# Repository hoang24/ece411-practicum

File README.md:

# Team 4: ECE 411 Practicum Repo

This is Team 4's Github repo for ECE411 Practicum. Codes and documents such as Product Design Specification (PDS) and Project Ideas can be found here.

### Team members:
- Jonathan Christian
- Hoang Nguyen
- Ngan Ho
- Karla Barraza

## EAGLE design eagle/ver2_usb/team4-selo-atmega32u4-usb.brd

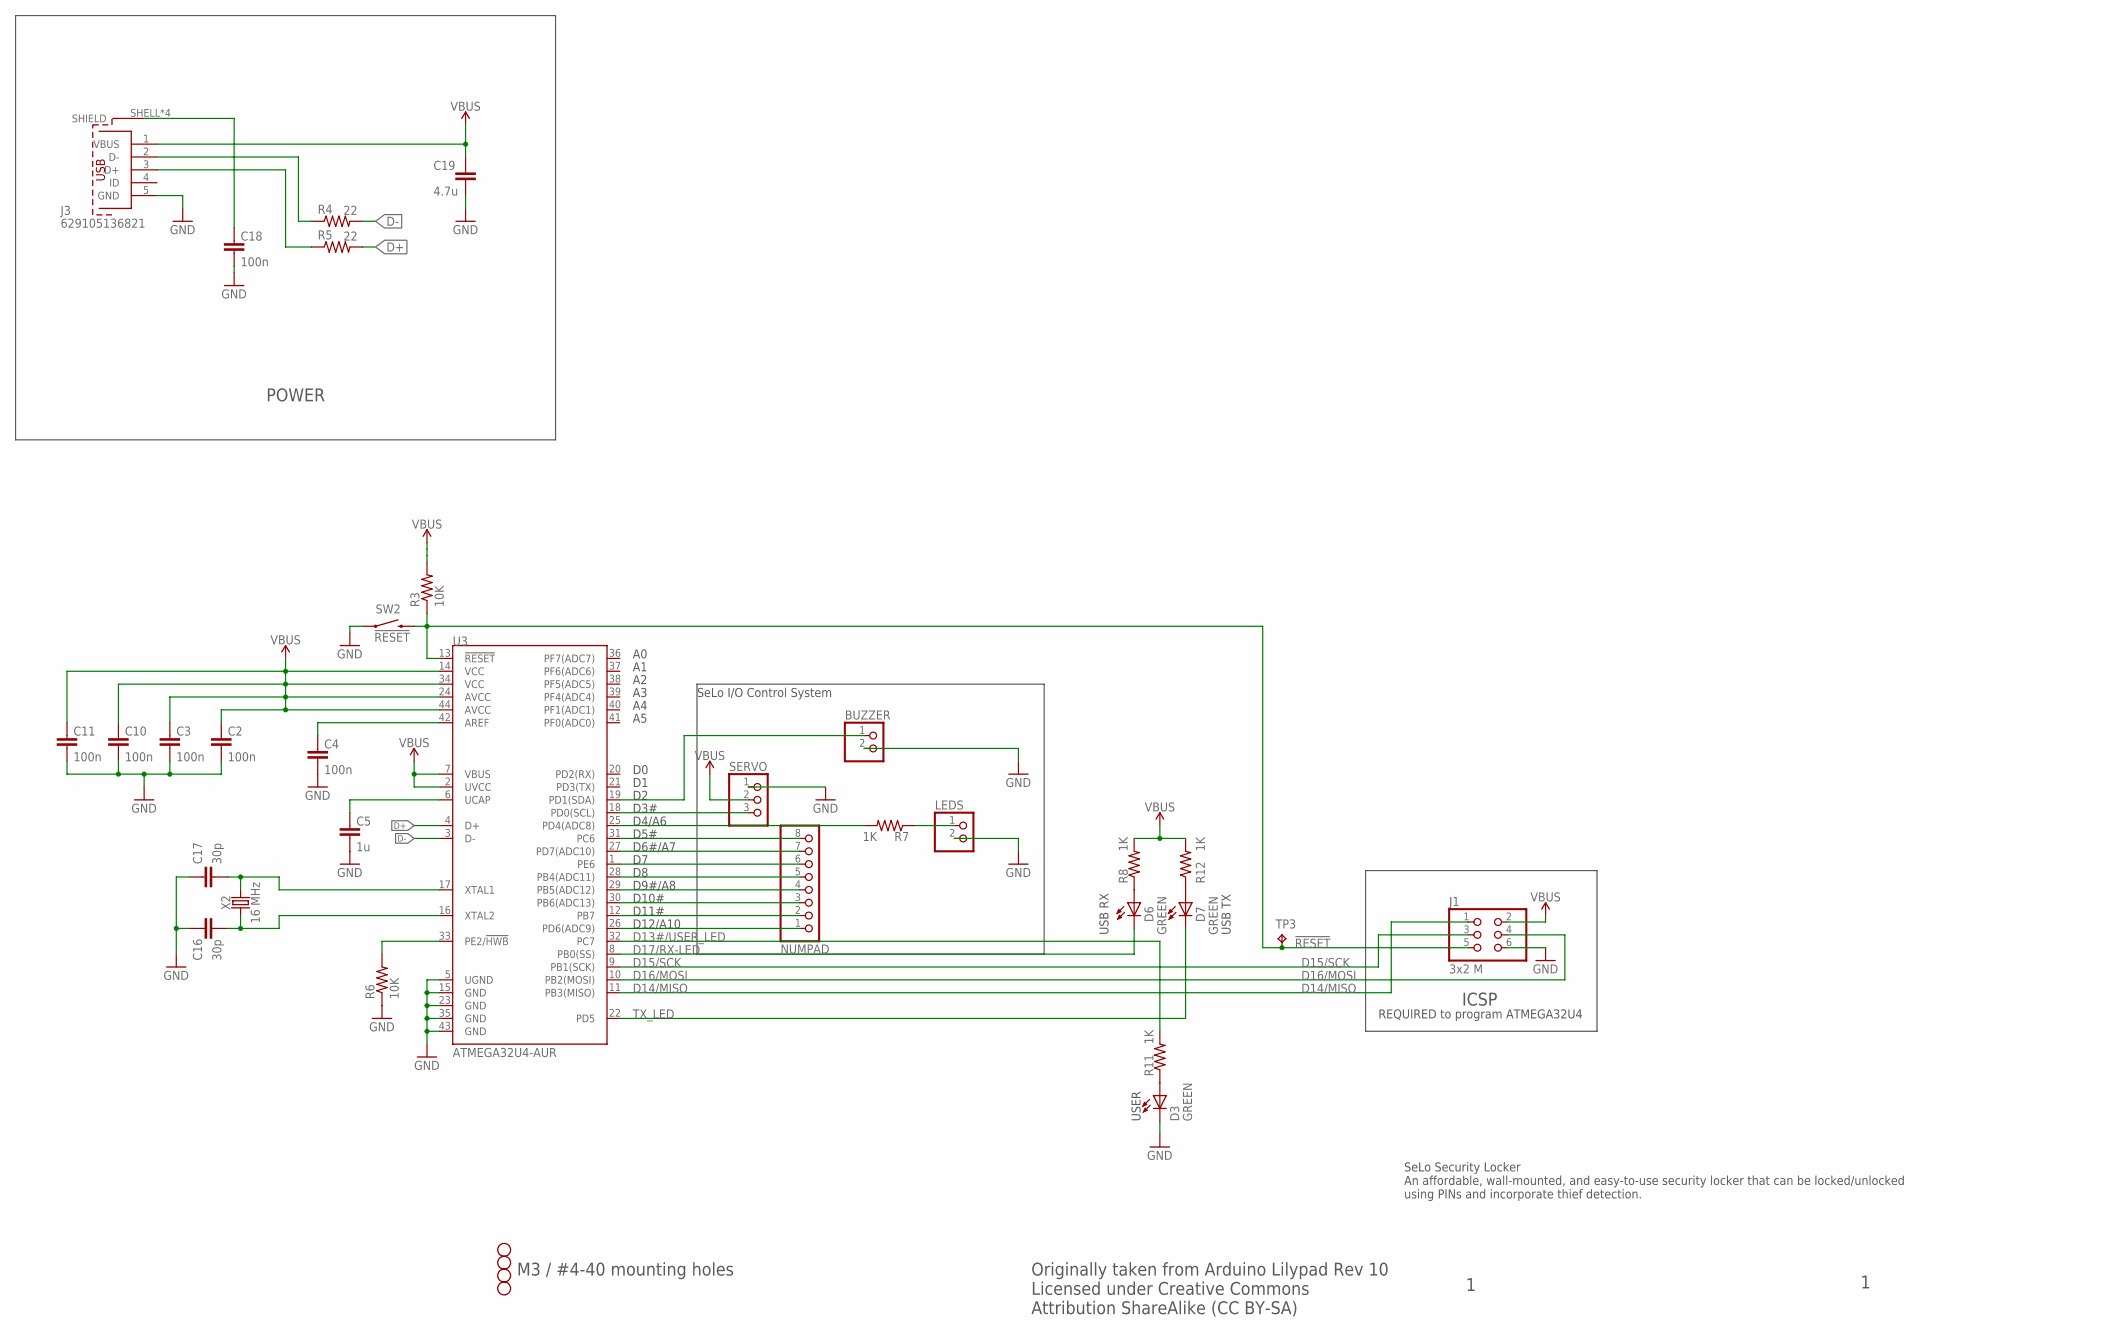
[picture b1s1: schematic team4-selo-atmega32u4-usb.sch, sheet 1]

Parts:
BUZZER: PINHD-1X2; 1X02
C2, C3, C4, C10, C11, C18: 100n; C0805K; MPN CL21B104KBCNNNC
C5: 1u; C0805K; MPN CL21B105KOFNNNG
C16: 30p; C0805K; MPN CL21C300JBANNNC
C17: 30p; C0805K; MPN CL21C180JBANNNC
C19: 4.7u; C0805K; MPN CL21A475KOFNNNE
D3, D6, D7: GREEN; CHIP-LED0805; MPN 150080GS75000
H1, H2, H3, H4: STAND-OFF
J1: 3x2 M; 2X03; MPN M20-9980345
J3: 629105136821; MPN 629105136821
LEDS: PINHD-1X2; 1X02
NUMPAD: PINHD-1X8; 1X08
R3, R6: 10K; R0805; MPN RC0805FR-0710KL
R4, R5: 22; R0805; MPN RC0805FR-0722RL
R7, R8, R11, R12: 1K; R0805; MPN RC0805FR-071KL
SERVO: PINHD-1X3; 1X03
SW2: !RESET; TACTILE_SWITCH_SMD; MPN RS-187R05A2-DS MT RT
TP3: TPPAD1-13; P1-13
U3: ATMEGA32U4-AUR; TQFP44; MPN ATMEGA32U4-AUR
X2: 16 MHz; HC49UP; MPN ECS-160-18-5PX-TR

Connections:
!RESET: J1.5, R3.1, SW2.3 (2), TP3.TP, U3.13 (!RESET)
AREF: C4.1, U3.42 (AREF)
D13#/USER_LED: R11.2, U3.32 (PC7)
D14/MISO: J1.1, U3.11 (PB3(MISO))
D15/SCK: J1.3, U3.9 (PB1(SCK))
D16/MOSI: J1.4, U3.10 (PB2(MOSI))
D17/RX-LED: D6.C, U3.8 (PB0(SS))
D+: R5.2, U3.4 (D+)
D-: R4.2, U3.3 (D-)
GND: BUZZER.2, C2.2, C3.2, C4.2, C5.2, C10.2, C11.2, C16.2, C17.2, C18.2, C19.2, D3.C, J1.6, J3.5 (GND), LEDS.2, R6.1, SERVO.1, SW2.1, U3.5 (UGND), U3.15 (GND), U3.23 (GND), U3.35 (GND), U3.43 (GND)
unnamed: SERVO.3, U3.18 (PD0(SCL))
unnamed: NUMPAD.8, U3.31 (PC6)
unnamed: NUMPAD.7, U3.27 (PD7(ADC10))
unnamed: NUMPAD.6, U3.1 (PE6)
unnamed: NUMPAD.5, U3.28 (PB4(ADC11))
unnamed: NUMPAD.4, U3.29 (PB5(ADC12))
unnamed: NUMPAD.3, U3.30 (PB6(ADC13))
unnamed: NUMPAD.2, U3.12 (PB7)
unnamed: NUMPAD.1, U3.26 (PD6(ADC9))
unnamed: D3.A, R11.1
unnamed: C18.1, J3.SHELL (SHIELD), J3.SHELL1 (SHIELD), J3.SHELL2 (SHIELD), J3.SHELL3 (SHIELD)
unnamed: D6.A, R8.1
unnamed: D7.A, R12.1
unnamed: R7.2, U3.25 (PD4(ADC8))
unnamed: LEDS.1, R7.1
unnamed: J3.2 (D-), R4.1
unnamed: J3.3 (D+), R5.1
unnamed: BUZZER.1, U3.19 (PD1(SDA))
PE2/!HWB: R6.2, U3.33 (PE2/!HWB)
TX_LED: D7.C, U3.22 (PD5)
UCAP: C5.1, U3.6 (UCAP)
VBUS: C2.1, C3.1, C10.1, C11.1, C19.1, J1.2, J3.1 (VBUS), R3.2, R8.2, R12.2, SERVO.2, U3.2 (UVCC), U3.7 (VBUS), U3.14 (VCC), U3.24 (AVCC), U3.34 (VCC), U3.44 (AVCC)
XTAL1: C17.1, U3.17 (XTAL1), X2.2
XTAL2: C16.1, U3.16 (XTAL2), X2.1

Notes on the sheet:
Originally taken from Arduino Lilypad Rev 10 Licensed under Creative Commons Attribution ShareAlike (CC BY-SA)
POWER
M3 / #4-40 mounting holes
ICSP
REQUIRED to program ATMEGA32U4
USB RX
USB TX
USER
D3#
D4/A6
D5#
D6#/A7
D9#/A8
D10#
D11#
D12/A10
SeLo I/O Control System
SeLo Security Locker An affordable, wall-mounted, and easy-to-use security locker that can be locked/unlocked using PINs and incorporate thief detection.

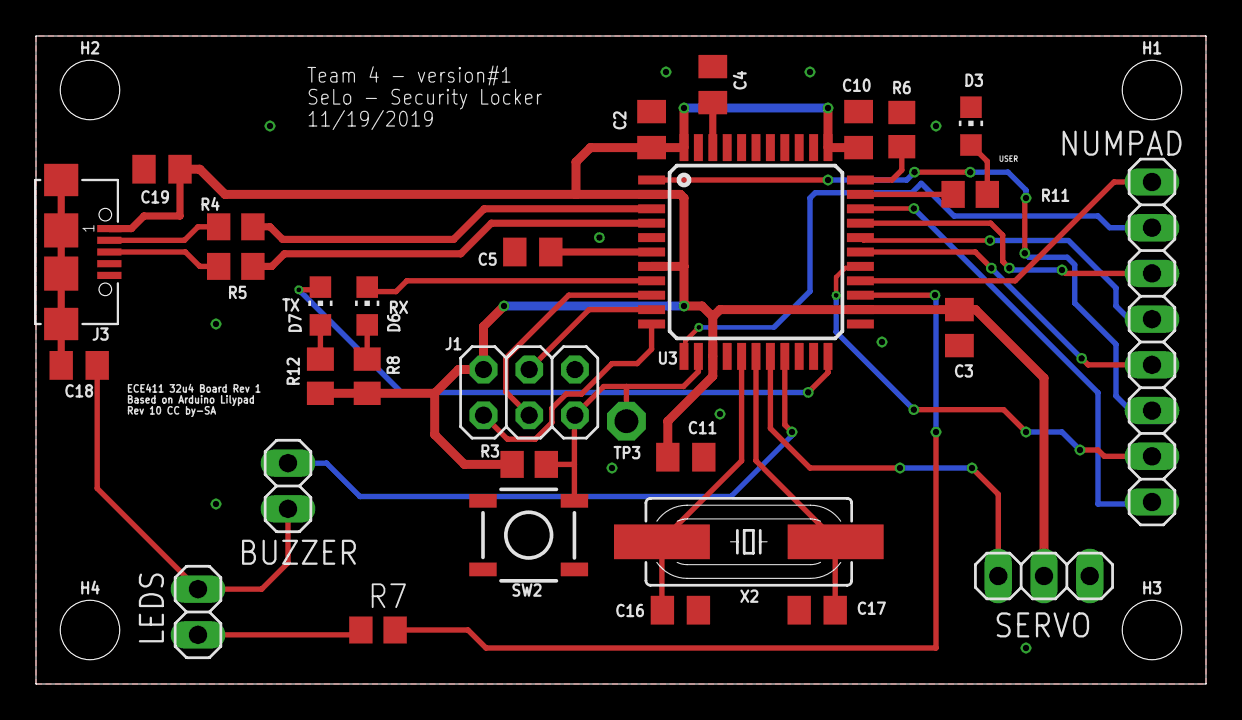
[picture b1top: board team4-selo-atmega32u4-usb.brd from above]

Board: 2 copper layers, 65.0 x 36.0 mm, 35 parts (0 on the bottom side), 34 nets.

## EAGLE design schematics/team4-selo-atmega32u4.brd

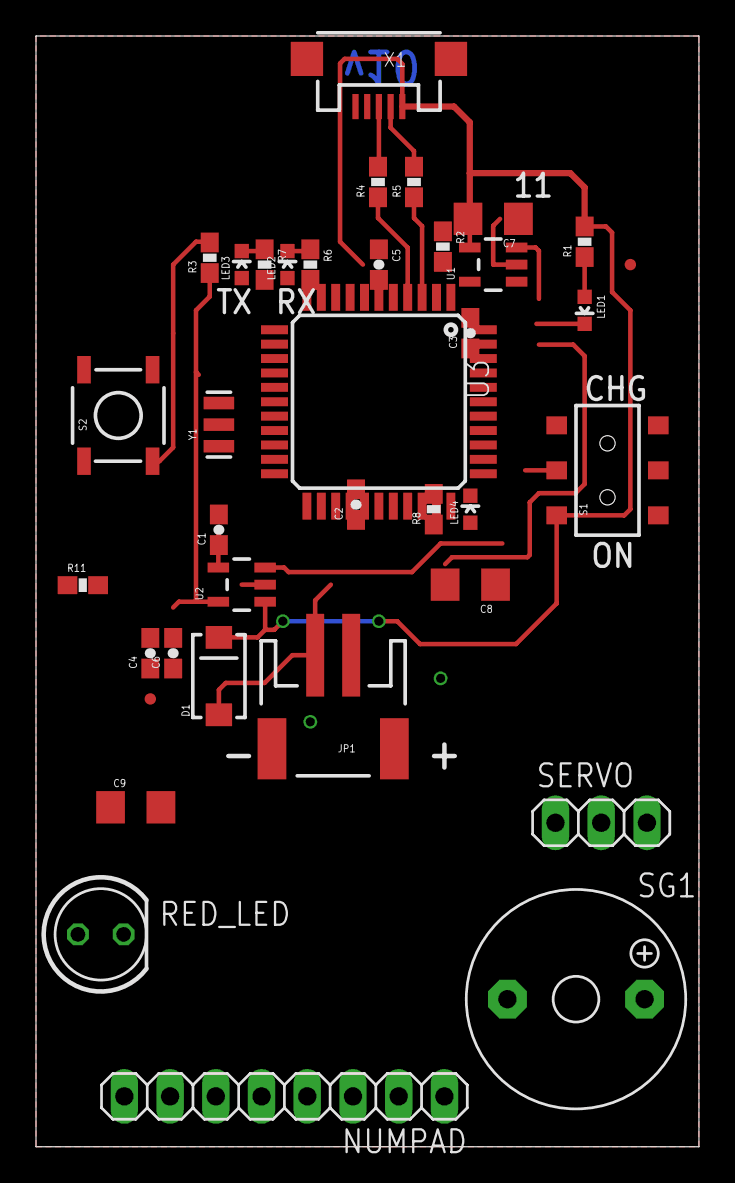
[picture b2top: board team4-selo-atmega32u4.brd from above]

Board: 2 copper layers, 36.8 x 61.7 mm, 37 parts (0 on the bottom side), 33 nets.

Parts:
C1: 470pF; 0603-CAP
C2, C3, C4: .1uF; 0603-CAP
C5: 1uF; 0603-CAP
C6: 4.7uF; 0603-CAP
C7, C8, C9: 4.7uF; 1206
D1: B340A; SMA-DIODE
JP1: JST-2; JST-2-SMD
JP2, JP3: FIDUCIALUFIDUCIAL; MICRO-FIDUCIAL
LED1, LED2, LED3, LED4: RED; LED-0603
NUMPAD: 1X08
R1, R6, R7, R8, R11: 330; 0603-RES
R2, R3: 10k; 0603-RES
R4, R5: 22; 0603-RES
RED_LED: LED5MM
S1: SWITCH-DPDTSMD; AYZ0202
S2: !RESET; TACTILE_SWITCH_SMD
SERVO: 1X03
SG1: F/TMB
U1: MCP73831; SOT23-5
U2: MIC5219; SOT23-5
U3: 32U4; TQFP44
X1: USB-MICROB
Y1: 8MHz; RESONATOR-SMD

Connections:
3.3V: C2.2, C3.2, C4.2, C5.2, C6.2, LED2.A, LED3.A, R3.1, U2.5, U3.6, U3.14, U3.24, U3.34, U3.42, U3.44
5V: C7.2, C9.2, D1.C, R1.2, S1.1, SERVO.2, U1.4, U2.1, U3.7, X1.VBUS
D+: R4.1, U3.4
D-: R5.1, U3.3
GND: C1.2, C2.1, C3.1, C4.1, C5.1, C6.1, C7.1, C8.1, C9.1, JP1.1, LED4.C, R2.1, RED_LED.K, S1.3, S2.1, SERVO.1, SG1.+, U1.2, U2.2, U3.5, U3.15, U3.23, U3.33, U3.35, U3.43, X1.GND, X1.MT1, X1.MT2, Y1.2
unnamed: LED2.C, R6.1
unnamed: S1.2, U2.3
unnamed: LED1.A, R1.1
unnamed: LED1.C, U1.1
unnamed: U3.17, Y1.1
unnamed: R2.2, U1.5
unnamed: U3.16, Y1.3
unnamed: C1.1, U2.4
unnamed: NUMPAD.8, U3.27
unnamed: NUMPAD.7, U3.1
unnamed: NUMPAD.6, U3.28
unnamed: NUMPAD.5, U3.29
unnamed: NUMPAD.4, U3.30
unnamed: NUMPAD.3, U3.12
unnamed: NUMPAD.2, U3.26
unnamed: SERVO.3, U3.18
unnamed: SG1.-, U3.31
unnamed: LED4.A, R8.1
unnamed: R5.2, X1.D-
unnamed: R4.2, X1.D+
unnamed: LED3.C, R7.1
unnamed: R11.2, U3.25
unnamed: R11.1, RED_LED.A
RESET: R3.2, S2.3, U3.13
RX_LED: R6.2, U3.8
TX_LED: R7.2, U3.22
USER_LED: NUMPAD.1, R8.2, U3.32
V_BATT: C8.2, D1.A, JP1.2, U1.3

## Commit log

2019-10-12 Upload planning document for top 3 ideas
2019-10-12 add markdown file for project ideas
2019-10-15 Update project_ideas.md
    add more descriptions for Interactive Panel for PSU Campus Map
2019-10-17 Indicate chosen project
2019-10-17 Update formatting
2019-10-17 Update project_ideas.md
    minor edit
2019-10-17 Create HW#2 Requirements
2019-10-17 Update HW#2 Requirements
2019-10-19 Create Practicum_Homework3
2019-10-19 Update Practicum_Homework3
2019-10-22 Rename Practicum_Homework3 to Practicum_Homework3.md
2019-10-23 remove unnecessary files, rename PDS file
2019-10-23 move images into 1 folder
2019-10-23 update PDS
2019-10-24 Small changes.
2019-10-29 add codes for prototype 1
2019-10-29 Commit code to control pinpad
    Checks and verifies password is correct.
2019-10-29 Allow password to be re-entered
2019-10-29 Update comments
2019-10-30 rename code files
2019-10-30 Create Input&OutputCombo
2019-10-30 add io combo codes
2019-10-31 integrate lock/unlock and theft detection features
2019-10-31 add pictures and video of 1st prototype
2019-10-31 Create new folder
    ,
2019-10-31 Upload initial schematic
2019-10-31 Update minor info changes
2019-11-05 Create Project Schedule
2019-11-05 update selo schematics
2019-11-07 put eagle files to archives
2019-11-07 add new eagle files
2019-11-07 update eagle schematic and board
2019-11-07 Updating tasks 40, 41, and 46
2019-11-11 Add bill of materials
2019-11-14 rename and delete unnecessary files
2019-11-14 edit board layout file
2019-11-14 move battery version board and schematics to archives
2019-11-14 Update BOM
2019-11-14 upload PDS, project schedule, design details
2019-11-16 reroute on eagle board, update gitignore
2019-11-18 update eagle board
2019-11-18 check with DRC
2019-11-18 add info to schematic
2019-11-19 Update code for 328p dev board
2019-11-19 update gitignore
2019-11-19 update board layout
2019-11-20 update board and schematic
2019-11-20 Add updates to project design specification
2019-11-20 edit tnames layer
2019-11-21 final update to eagle board
2019-11-21 add ratsnet
2019-11-21 Create Design Review
2019-11-21 Update Design Review
2019-11-21 Rename Design Review to Design_Review.md
2019-12-02 Refactor key press read functionality, allow password changes. Requires testing
2019-12-04 update code, controlSys_2 works on PCB
2019-12-04 add 2 testcases for LED and servo
2019-12-04 Debugged password change code
2019-12-06 Final code: add beeps for key presses
2019-12-06 Fix random apostrophe
2019-12-06 Change open position at startup
2019-12-09 rearrage documents in repo
2019-12-09 rename documents, add test plan for SeLo
2019-12-09 add sound for changing password, sound at the end of a sequence
2019-12-09 remove redundant files, create backup codes
2019-12-10 Add files via upload
    Add new BOM
2019-12-10 Delete Product_BOM.xlsx
    Updating BOM, removing old one
2019-12-10 update PDS to rev. 3, rearrage BOM

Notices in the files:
eagle/ver2_usb/team4-selo-atmega32u4-usb.brd:
Rev 10 CC by-SA
parts and their libraries:
SparkFun-Electromechanical: Licensing: CC v3.0 Share-Alike You are welcome to use this library for commercial purposes.
SparkFun-IC-Microcontroller: Licensing: Creative Commons ShareAlike 4.0 International - https://creativecommons.org/licenses/by-sa/4.0
